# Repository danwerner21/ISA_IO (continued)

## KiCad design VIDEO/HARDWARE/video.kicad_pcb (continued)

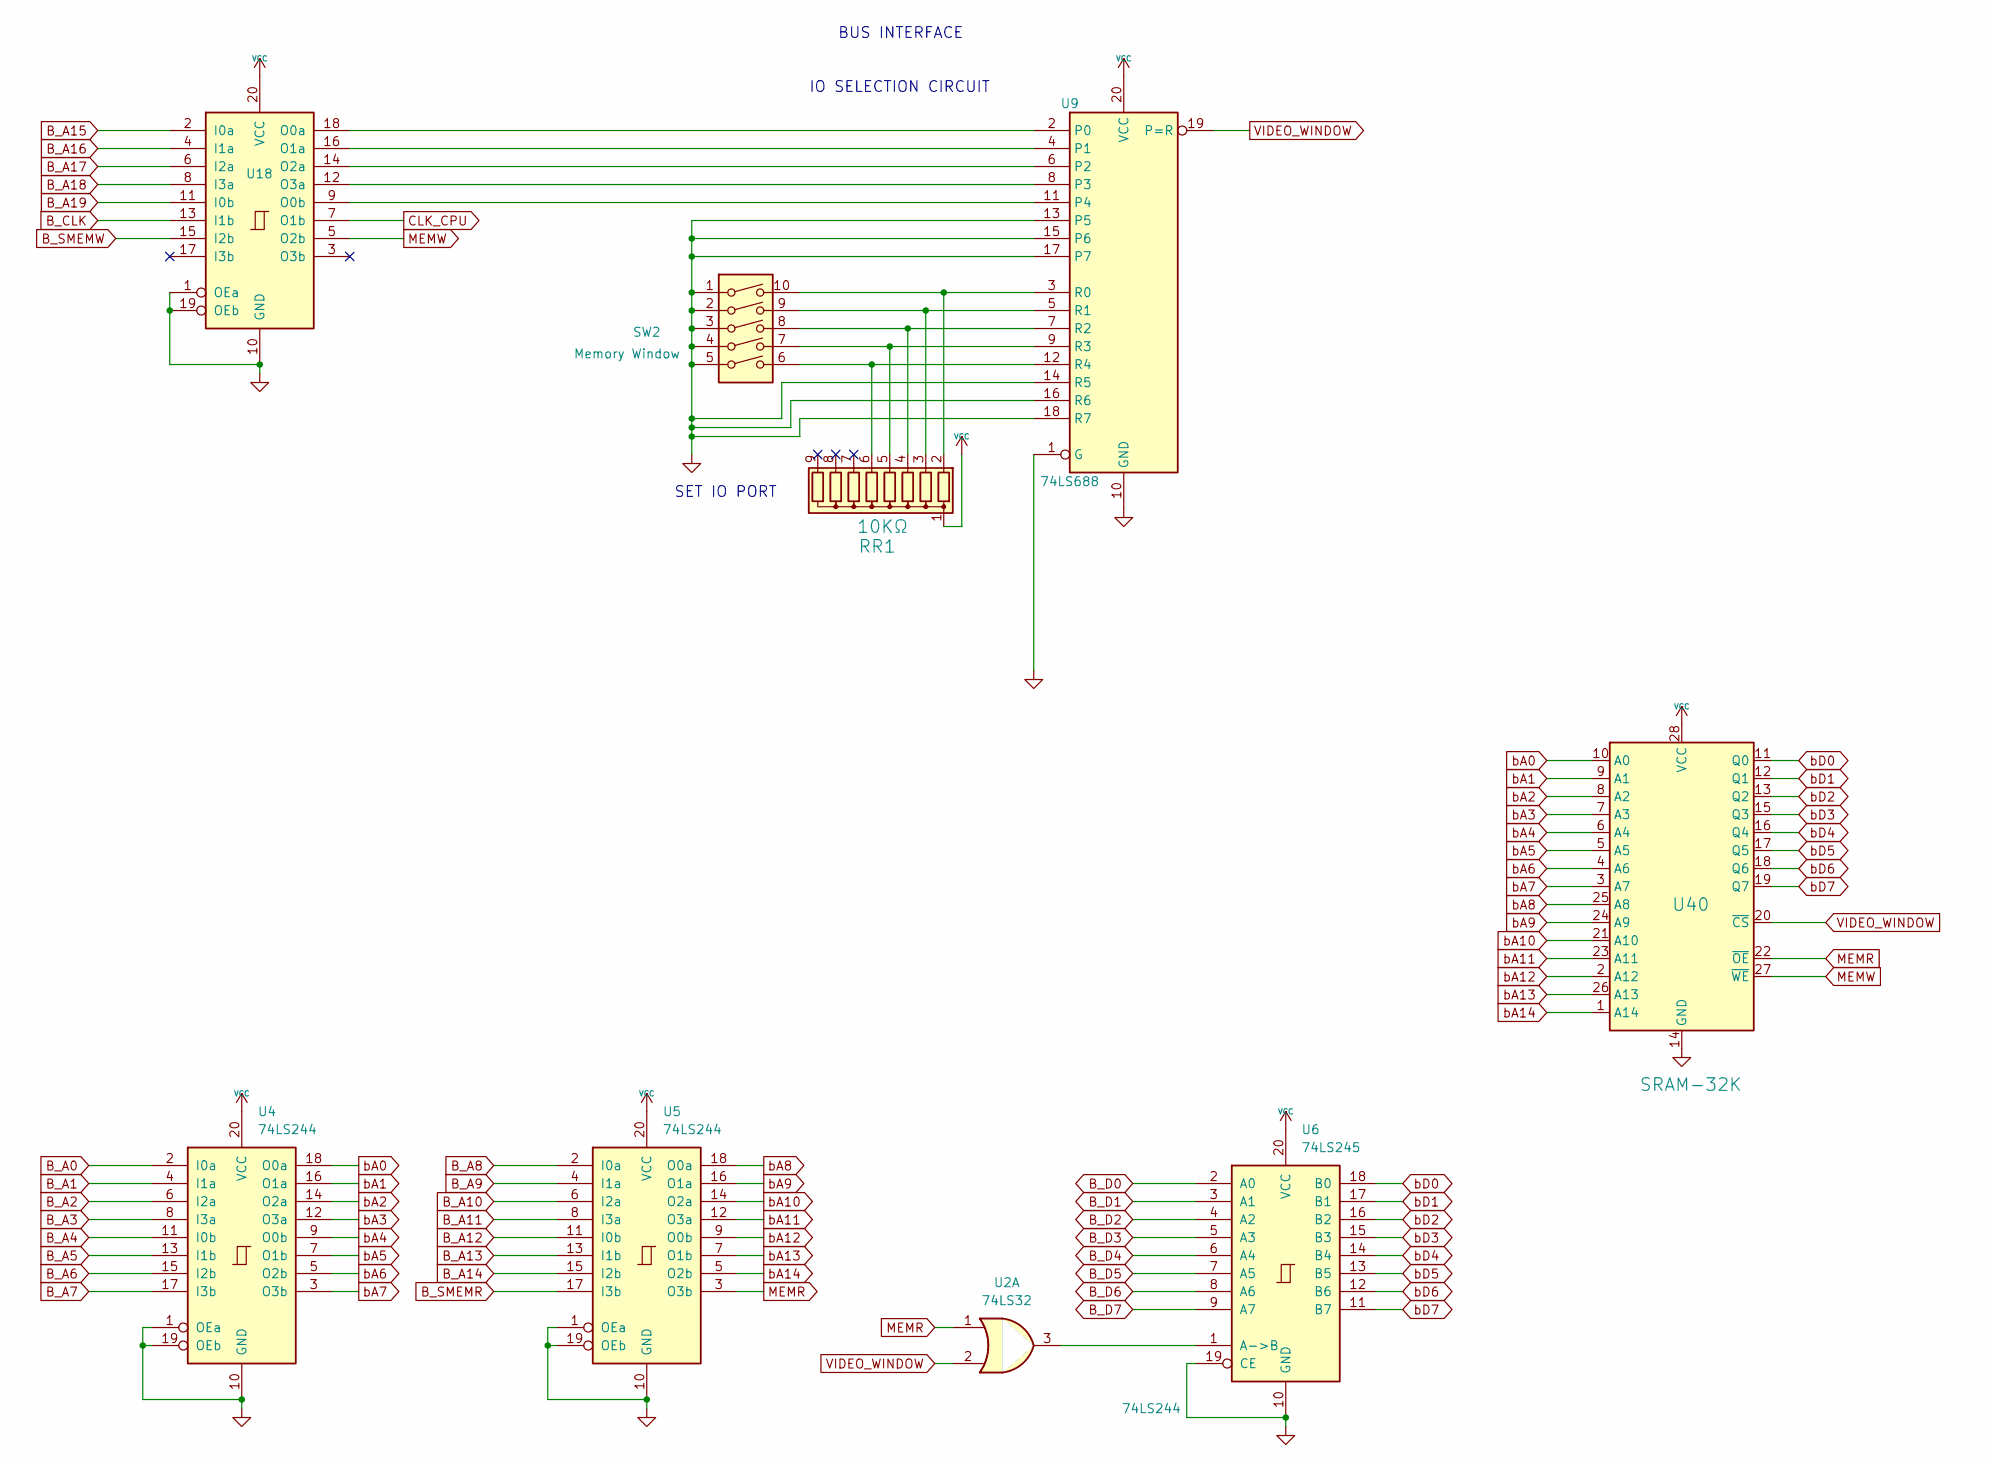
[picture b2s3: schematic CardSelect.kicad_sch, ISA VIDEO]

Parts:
RR1: 10KΩ; STD_DDW_SIP9
SW2: Memory Window; STD_DDW_DIP10
U2: 74LS32; STD_DDW_DIP14
U4, U5, U18: 74LS244; STD_DDW_DIP20
U6: 74LS245; STD_DDW_DIP20
U9: 74LS688; STD_DDW_DIP20
U40: SRAM-32K; STD_DDW_DIP28_SKINNY

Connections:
B_A0: U4.2 (I0a); also elsewhere on the board
B_A1: U4.4 (I1a); also elsewhere on the board
B_A2: U4.6 (I2a); also elsewhere on the board
B_A3: U4.8 (I3a); also elsewhere on the board
B_A4: U4.11 (I0b); also elsewhere on the board
B_A5: U4.13 (I1b); also elsewhere on the board
B_A6: U4.15 (I2b); also elsewhere on the board
B_A7: U4.17 (I3b); also elsewhere on the board
B_A8: U5.2 (I0a); also elsewhere on the board
B_A9: U5.4 (I1a); also elsewhere on the board
B_A10: U5.6 (I2a); also elsewhere on the board
B_A11: U5.8 (I3a); also elsewhere on the board
B_A12: U5.11 (I0b); also elsewhere on the board
B_A13: U5.13 (I1b); also elsewhere on the board
B_A14: U5.15 (I2b); also elsewhere on the board
B_A15: U18.2 (I0a); also elsewhere on the board
B_A16: U18.4 (I1a); also elsewhere on the board
B_A17: U18.6 (I2a); also elsewhere on the board
B_A18: U18.8 (I3a); also elsewhere on the board
B_A19: U18.11 (I0b); also elsewhere on the board
B_CLK: U18.13 (I1b); also elsewhere on the board
B_D0: U6.2 (A0); also elsewhere on the board
B_D1: U6.3 (A1); also elsewhere on the board
B_D2: U6.4 (A2); also elsewhere on the board
B_D3: U6.5 (A3); also elsewhere on the board
B_D4: U6.6 (A4); also elsewhere on the board
B_D5: U6.7 (A5); also elsewhere on the board
B_D6: U6.8 (A6); also elsewhere on the board
B_D7: U6.9 (A7); also elsewhere on the board
B_SMEMR: U5.17 (I3b); also elsewhere on the board
B_SMEMW: U18.15 (I2b); also elsewhere on the board
CLK_CPU: U18.7 (O1b); also elsewhere on the board
GND: SW2.1, SW2.2, SW2.3, SW2.4, SW2.5, U4.1 (OEa), U4.10 (GND), U4.19 (OEb), U5.1 (OEa), U5.10 (GND), U5.19 (OEb), U6.10 (GND), U6.19 (CE), U9.1 (G), U9.10 (GND), U9.13 (P5), U9.14 (R5), U9.15 (P6), U9.16 (R6), U9.17 (P7), U9.18 (R7), U18.1 (OEa), U18.10 (GND), U18.19 (OEb), U40.14 (GND); also elsewhere on the board
MEMR: U2.1, U5.3 (O3b), U40.22 (~OE)
MEMW: U18.5 (O2b), U40.27 (~WE); also elsewhere on the board
unnamed: RR1.2 (R1), SW2.10, U9.3 (R0)
unnamed: RR1.3 (R2), SW2.9, U9.5 (R1)
unnamed: RR1.4 (R3), SW2.8, U9.7 (R2)
unnamed: RR1.5 (R4), SW2.7, U9.9 (R3)
unnamed: RR1.6 (R5), SW2.6, U9.12 (R4)
unnamed: U2.3, U6.1 (A->B)
unnamed: U9.2 (P0), U18.18 (O0a)
unnamed: U9.11 (P4), U18.9 (O0b)
unnamed: U9.4 (P1), U18.16 (O1a)
unnamed: U9.6 (P2), U18.14 (O2a)
unnamed: U9.8 (P3), U18.12 (O3a)
VCC: RR1.1 (common), U4.20 (VCC), U5.20 (VCC), U6.20 (VCC), U9.20 (VCC), U18.20 (VCC), U40.28 (VCC); also elsewhere on the board
VIDEO_WINDOW: U2.2, U9.19 (P=R), U40.20 (~CS); also elsewhere on the board
bA0: U4.18 (O0a), U40.10 (A0)
bA1: U4.16 (O1a), U40.9 (A1)
bA2: U4.14 (O2a), U40.8 (A2)
bA3: U4.12 (O3a), U40.7 (A3)
bA4: U4.9 (O0b), U40.6 (A4)
bA5: U4.7 (O1b), U40.5 (A5)
bA6: U4.5 (O2b), U40.4 (A6)
bA7: U4.3 (O3b), U40.3 (A7)
bA8: U5.18 (O0a), U40.25 (A8)
bA9: U5.16 (O1a), U40.24 (A9)
bA10: U5.14 (O2a), U40.21 (A10)
bA11: U5.12 (O3a), U40.23 (A11)
bA12: U5.9 (O0b), U40.2 (A12)
bA13: U5.7 (O1b), U40.26 (A13)
bA14: U5.5 (O2b), U40.1 (A14)
bD0: U6.18 (B0), U40.11 (Q0); also elsewhere on the board
bD1: U6.17 (B1), U40.12 (Q1); also elsewhere on the board
bD2: U6.16 (B2), U40.13 (Q2); also elsewhere on the board
bD3: U6.15 (B3), U40.15 (Q3); also elsewhere on the board
bD4: U6.14 (B4), U40.16 (Q4); also elsewhere on the board
bD5: U6.13 (B5), U40.17 (Q5); also elsewhere on the board
bD6: U6.12 (B6), U40.18 (Q6); also elsewhere on the board
bD7: U6.11 (B7), U40.19 (Q7); also elsewhere on the board

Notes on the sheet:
SET IO PORT
IO SELECTION CIRCUIT
BUS INTERFACE

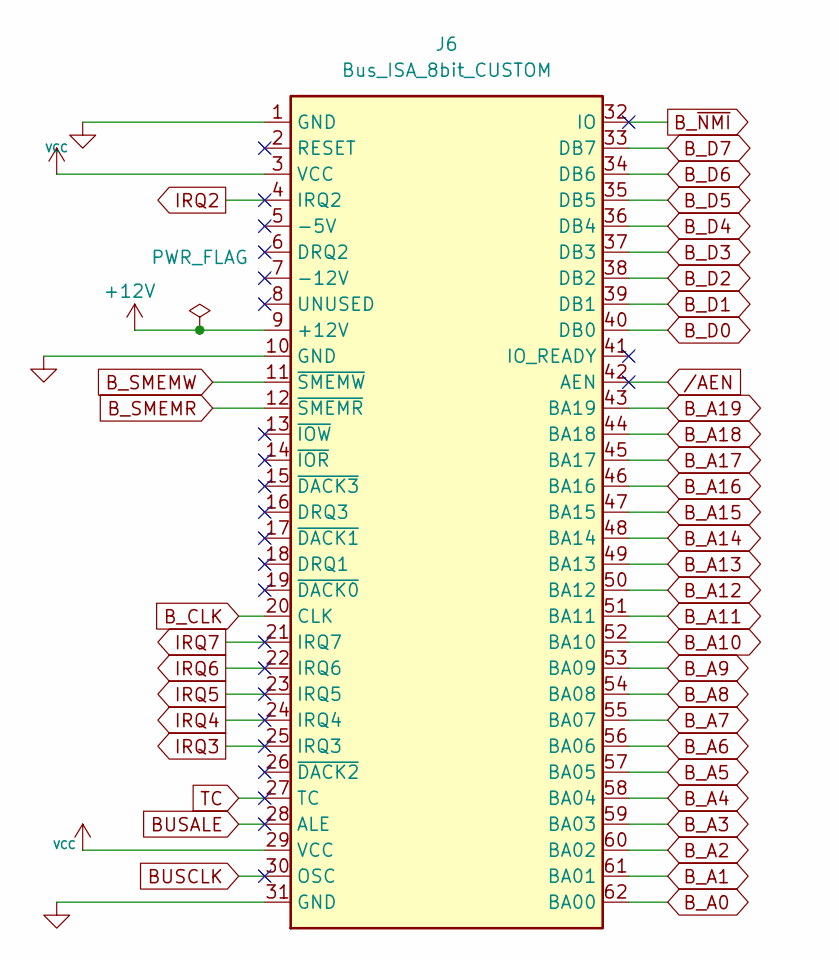
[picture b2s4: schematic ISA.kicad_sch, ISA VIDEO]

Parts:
J6: Bus_ISA_8bit_CUSTOM; BUSEDGE_XT

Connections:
+12V: J6.9 (+12V)
BUSALE: J6.28 (ALE)
BUSCLK: J6.30 (OSC)
B_A0: J6.62 (BA00); also elsewhere on the board
B_A1: J6.61 (BA01); also elsewhere on the board
B_A2: J6.60 (BA02); also elsewhere on the board
B_A3: J6.59 (BA03); also elsewhere on the board
B_A4: J6.58 (BA04); also elsewhere on the board
B_A5: J6.57 (BA05); also elsewhere on the board
B_A6: J6.56 (BA06); also elsewhere on the board
B_A7: J6.55 (BA07); also elsewhere on the board
B_A8: J6.54 (BA08); also elsewhere on the board
B_A9: J6.53 (BA09); also elsewhere on the board
B_A10: J6.52 (BA10); also elsewhere on the board
B_A11: J6.51 (BA11); also elsewhere on the board
B_A12: J6.50 (BA12); also elsewhere on the board
B_A13: J6.49 (BA13); also elsewhere on the board
B_A14: J6.48 (BA14); also elsewhere on the board
B_A15: J6.47 (BA15); also elsewhere on the board
B_A16: J6.46 (BA16); also elsewhere on the board
B_A17: J6.45 (BA17); also elsewhere on the board
B_A18: J6.44 (BA18); also elsewhere on the board
B_A19: J6.43 (BA19); also elsewhere on the board
B_CLK: J6.20 (CLK); also elsewhere on the board
B_D0: J6.40 (DB0); also elsewhere on the board
B_D1: J6.39 (DB1); also elsewhere on the board
B_D2: J6.38 (DB2); also elsewhere on the board
B_D3: J6.37 (DB3); also elsewhere on the board
B_D4: J6.36 (DB4); also elsewhere on the board
B_D5: J6.35 (DB5); also elsewhere on the board
B_D6: J6.34 (DB6); also elsewhere on the board
B_D7: J6.33 (DB7); also elsewhere on the board
B_SMEMR: J6.12 (~SMEMR); also elsewhere on the board
B_SMEMW: J6.11 (~SMEMW); also elsewhere on the board
B_~NMI: J6.32 (IO)
GND: J6.1 (GND), J6.10 (GND), J6.31 (GND); also elsewhere on the board
IRQ2: J6.4 (IRQ2)
IRQ3: J6.25 (IRQ3)
IRQ4: J6.24 (IRQ4)
IRQ5: J6.23 (IRQ5)
IRQ6: J6.22 (IRQ6)
IRQ7: J6.21 (IRQ7)
TC: J6.27 (TC)
VCC: J6.3 (VCC), J6.29 (VCC); also elsewhere on the board
/AEN: J6.42 (AEN)

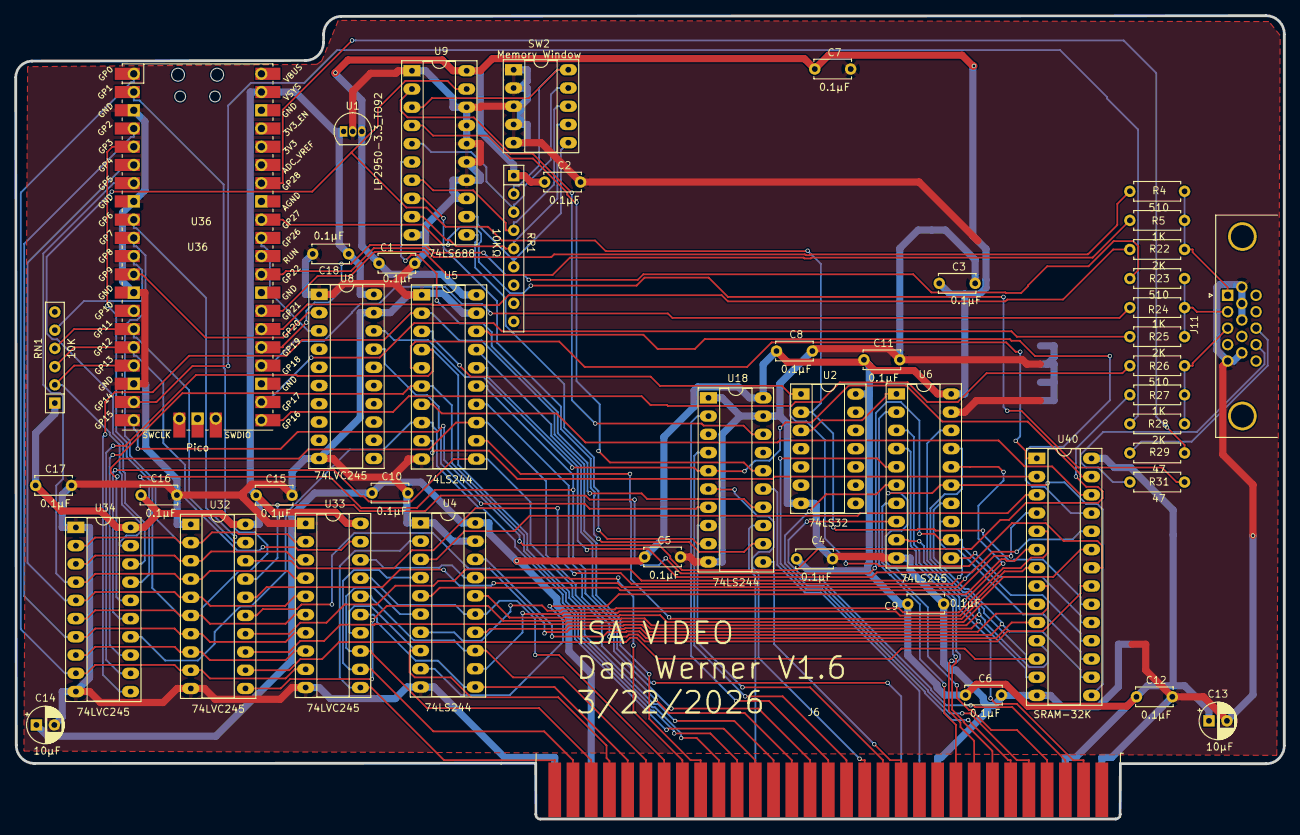
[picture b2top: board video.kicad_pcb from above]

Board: 2 copper layers, 176.7 x 111.9 mm, 47 parts (0 on the bottom side), 102 nets.

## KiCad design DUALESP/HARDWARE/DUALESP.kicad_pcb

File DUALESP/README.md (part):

# ESP32 Multi IO
The Nhyodyne ESP32 board provides the following functions for your Nhyodyne computer
* ANSI Console
* Graphics
* Sprites
* Sound
* Dual USB Serial Support
* WiFi
* Keyboard
* Mouse

This board relies heavily on the FabGL library from Fabrizio Di Vittorio.   More information can be found [HERE](http://www.fabglib.org/)

# BUGS

Version 1.0 is unusable

Version 1.1 is missing some data line connections
* Connect U11 Pin 11 to U13 Pin 15
* Connect U11 Pin 12 to U13 Pin 1
* Connect U11 Pin 13 to U13 Pin 2
* Connect U11 Pin 14 to U13 Pin 3
* Connect U11 Pin 3 to U13 Pin 4
* Connect U11 Pin 4 to U13 Pin 5
* Connect U11 Pin 5 to U13 Pin 6
* Connect U11 Pin 6 to U13 Pin 7

Version 1.2 has not been verified, but should be correct

# ESP32 BOM
Qty|Reference(s)|Value|Notes
---|------------|-----|-----
12|C1, C2, C3, C4, C5, C6, C7, C8, C9, C10, C13, C14|0.1uF
3|C11, C12, C16|10uF
1|C15|100nf
1|D2|LED
2|D3, D6|1N4001
1|J3|Pin Header, right angle 1x2
1|J4|Pin Header, right angle 1x3
1|J5|Pin Header, right angle 1x3
1|J6|DB15 Female High Density PCB VGA Connector
1|J7|Pin Header, right angle 2x5
1|P2|Pin Header Right Angle 2x25
4|R1, R3, R14, R15|120ohm
1|R2|470ohm
2|R4, R6|2Kohm
2|R5, R13|1Kohm
3|R7, R9, R11|400ohm
3|R8, R10, R12|800ohm
1|R16|270ohm
1|R17|150ohm
1|RR1|10Kohm, networked, 9 pin, 8 resistor
1|RR2|1Kohm, networked, 9 pin, 8 resistor
1|SW1|8 position DIP switch
1|U1|74LS04
2|U2, U4|74LS244
1|U3|74LS245
3|U5, U6, U14|74LS32
2|U7, U9|74HC595
2|U8, U11|74HC165
1|U10|74LS688
2|U12, U13|ESP-WROOM-32 Dev Module|Such As: https://www.amazon.com/ESP-WROOM-32-Development-Microcontroller-Integrated-Compatible/dp/B08D5ZD528
1|U15|74LS244
1|U16|74LS07

# ESP32 Firmware Installation
The firmware for this board requires that platformio be installed on your system.

To install platformio core for your operating system see the directions [HERE](https://platformio.org/install/cli).  
Make sure you follow the additional directions to install the shell commands.

On linux systems it may be necessary to update permissions for the device that is autocreated for the ESP32. [More details](https://docs.platformio.org/en/latest/core/installation/udev-rules.html)  
Once platformio is properly setup on your system, you should be able to build and deploy the firmware to the ESP32.  

## To build and install the ESP firmware:
Take the ESP32 device you have designated as ESP0 and with it NOT INSTALLED in the nhyodyne card, plug it into your computer via USB.
change directory to the ESP0Firmware folder on your PC and from the operating system prompt type
```
pio run -t upload
```

Over the next couple of minutes you should see the build and upload process
something like this:

```
dwerner@lserver02:/lserver03/fileserv/Development/Vintage/Projects/nhyodyne/Z80ESP/ESP0Firmware$ pio run -t upload
Processing esp32dev (platform: espressif32; board: esp32dev; framework: arduino)
-----------------------------------------------------------------------------------------------------------------------
Verbose mode can be enabled via `-v, --verbose` option
CONFIGURATION: https://docs.platformio.org/page/boards/espressif32/esp32dev.html
PLATFORM: Espressif 32 (6.3.2) > Espressif ESP32 Dev Module
HARDWARE: ESP32 240MHz, 320KB RAM, 4MB Flash
DEBUG: Current (cmsis-dap) External (cmsis-dap, esp-bridge, esp-prog, iot-bus-jtag, jlink, minimodule, olimex-arm-usb-ocd, olimex-arm-usb-ocd-h, olimex-arm-usb-tiny-h, olimex-jtag-tiny, tumpa)
PACKAGES:
 - framework-arduinoespressif32 @ 3.20009.0 (2.0.9)
 - tool-esptoolpy @ 1.40501.0 (4.5.1)
 - tool-mkfatfs @ 2.0.1
 - tool-mklittlefs @ 1.203.210628 (2.3)
 - tool-mkspiffs @ 2.230.0 (2.30)
 - toolchain-xtensa-esp32 @ 8.4.0+2021r2-patch5
LDF: Library Dependency Finder -> https://bit.ly/configure-pio-ldf
LDF Modes: Finder ~ deep+, Compatibility ~ soft
Found 34 compatible libraries
Scanning dependencies...
Dependency Graph
|-- FabGL @ 1.0.9
|-- SPI @ 2.0.0
|-- Preferences @ 2.0.0
Building in release mode
Retrieving maximum program size .pio/build/esp32dev/firmware.elf
Checking size .pio/build/esp32dev/firmware.elf
Advanced Memory Usage is available via "PlatformIO Home > Project Inspect"
RAM:   [=         ]   9.3% (used 30632 bytes from 327680 bytes)
Flash: [=====     ]  46.4% (used 608561 bytes from 1310720 bytes)
Configuring upload protocol...
AVAILABLE: cmsis-dap, esp-bridge, esp-prog, espota, esptool, iot-bus-jtag, jlink, minimodule, olimex-arm-usb-ocd, olimex-arm-usb-ocd-h, olimex-arm-usb-tiny-h, olimex-jtag-tiny, tumpa
CURRENT: upload_protocol = esptool
Looking for upload port...
Auto-detected: /dev/ttyUSB0
Uploading .pio/build/esp32dev/firmware.bin
esptool.py v4.5.1
Serial port /dev/ttyUSB0
Connecting.....
Chip is ESP32-D0WD-V3 (revision v3.0)
Features: WiFi, BT, Dual Core, 240MHz, VRef calibration in efuse, Coding Scheme None
Crystal is 40MHz
MAC: 08:b6:1f:33:39:fc
Uploading stub...
Running stub...
Stub running...
Changing baud rate to 460800
Changed.
Configuring flash size...
Flash will be erased from 0x00001000 to 0x00005fff...
Flash will be erased from 0x00008000 to 0x00008fff...
Flash will be erased from 0x0000e000 to 0x0000ffff...
Flash will be erased from 0x00010000 to 0x000a4fff...
Compressed 17488 bytes to 12168...
Writing at 0x00001000... (100 %)
Wrote 17488 bytes (12168 compressed) at 0x00001000 in 0.5 seconds (effective 287.3 kbit/s)...
Hash of data verified.
Compressed 3072 bytes to 146...
Writing at 0x00008000... (100 %)
Wrote 3072 bytes (146 compressed) at 0x00008000 in 0.0 seconds (effective 571.2 kbit/s)...
Hash of data verified.
Compressed 8192 bytes to 47...
Writing at 0x0000e000... (100 %)
Wrote 8192 bytes (47 compressed) at 0x0000e000 in 0.1 seconds (effective 829.3 kbit/s)...
Hash of data verified.
Compressed 608928 bytes to 309667...
Writing at 0x00010000... (5 %)
Writing at 0x00020854... (10 %)
Writing at 0x0002f631... (15 %)
Writing at 0x0003b66a... (21 %)
Writing at 0x0004b725... (26 %)
Writing at 0x00050794... (31 %)
Writing at 0x00056585... (36 %)
Writing at 0x0005c2fd... (42 %)
Writing at 0x0006271e... (47 %)
Writing at 0x000684b2... (52 %)
Writing at 0x0006dceb... (57 %)
Writing at 0x00073098... (63 %)
Writing at 0x0007864e... (68 %)
Writing at 0x0007de33... (73 %)
Writing at 0x0008412b... (78 %)
Writing at 0x0008c053... (84 %)
Writing at 0x00094cba... (89 %)
Writing at 0x0009a559... (94 %)
Writing at 0x0009f9b7... (100 %)
Wrote 608928 bytes (309667 compressed) at 0x00010000 in 8.0 seconds (effective 606.6 kbit/s)...
Hash of data verified.

Leaving...
Hard resetting via RTS pin...
============================================ [SUCCESS] Took 22.49 seconds ============================================
```

Once this is done you can install ESP0 into U12 on your nhyodyne board.  Then repeat the process for the ESP1 and install into U13.

# ESP32 Communication Protocol

The ESP32 board communicates with your system via 3 ports, two IO ports and one status port.

The default configuration sets the base IO to $9C.  IO Communication with ESP0 is at base port, ESP1 is at base port +1 and the status register is at base port +2.

```
ESPBASE         EQU $9C         ; Base Port
ESP0:           EQU ESPBASE     ; ESP0 IO PORT

ESP1:           EQU ESPBASE+1   ; ESP1 IO PORT

ESP_STATUS:     EQU ESPBASE+2   ; ESP  STATUS PORT
                                ; MSB XX XX S S S S S
                                ;           | | | | |- ESP0 READY_OUTPUT
                                ;           | | | |--- ESP0 BUSY
                                ;           | | |----- ESP0 SPARE (unused)
                                ;           | |------- ESP1 READY_OUTPUT
                                ;           |--------- ESP1 BUSY
```

The communication process is fairly straight forward.  Upon reset, the ESP will initialize, set BUSY and READY_OUTPUT to low and wait for an opcode.

To send an opcode or data to the ESP:

* wait for ESPx BUSY bit to go low (a timeout is suggested)
* write the opcode or data to the ESPx IO port
* it is a best practice to wait for ESPx BUSY bit to go high then low (a timeout is suggested) before sending the next byte

If an "out of sync" occurrs, where the ESP is waiting for data rather than an opcode and the host driver is unsure of the state of the ESP, it is possible to resync the ESP back to the "waiting for opcode" state by sending a stream of NULL bytes to the IO port. A stream of more than 25 NULLS should always safely return the ESP back to the "waiting for opcode" state.

Some Opcodes will return one or more bytes to the host system.   For those opcodes

* wait for ESPx BUSY bit to go low (a timeout is suggested)
* wait for ESPx READY_OUTPUT bit to go high (a timeout is suggested)
* Read the ESPx IO port
* it is a best practice to wait for ESPx BUSY bit to go high then low (a timeout is suggested) before sending the next byte

Note that the BUSY bit transitions after a command is written or data is read can happen very fast.   On slower systems a timeout is required as it is possible for the host system to miss this transition if it is not polling fast enough.

It is also a best practice to empty the ESP send buffer before sending an opcode that returns data.

For example code, see the ESPTEST.ASM program in this repo.

# ESP32 ESP0 Opcode Reference

## ESP32 Misc Opcodes

OP CODE|Description|Values
-------|-----------|------
00|NO OPERATION|NONE

The NO OPERATION opcode is used to sync the ESP32 communications stream to a known state, "Waiting for opcode".

Input Parameters: None  
Returns: None  

OP CODE|Description|Values
-------|-----------|------
255|DISCOVER|"E" "S" "P" "3" "2" "V" "1"

The DISCOVER opcode is used by host systems to verify the presence and version of the ESP hardware and firmware.

Input Parameters: None  
Returns: 7 bytes - "E" "S" "P" "3" "2" "V" "1"  

## ESP32 Terminal Opcodes
	
OP CODE|Description|Values
-------|-----------|------
1 |VGA ANSI TERM OUT SINGLE CHAR| OUT-BYTE

The VGA ANSI TERM OUT SINGLE CHAR opcode sends a single byte to the ANSI terminal subsystem of the ESP32.  Using the ANSI escape sequence set, this byte is rendered to the VGA terminal console.

Input Parameters: 1 byte - "OUT CHAR"  
Returns: None  

OP CODE|Description|Values
-------|-----------|------
2 |VGA ANSI TERM OUT NULL TERMINATED STRING| OUT-BYTE	OUT-BYTE	OUT-BYTE	OUT-BYTE	OUT-BYTE	OUT-BYTE	…	…	…	…	NULL

The VGA ANSI TERM OUT NULL TERMINATED STRING opcode sends a null terminated string to the ANSI terminal subsystem of the ESP32.  Using the ANSI escape sequence set, this string is rendered to the VGA terminal console.

Input Parameters: X bytes - string terminated by a null  
Returns: None  

OP CODE|Description|Values
-------|-----------|------
3 |VGA ANSI TERM KEYBOARD IN| IN-BYTE	

The VGA ANSI TERM KEYBOARD IN opcode returns a byte from the terminal keyboard buffer.   If there is no keystrokes in the buffer, the opcode will return a null.

Input Parameters: None  
Returns: 1 byte - input keystroke or null  

OP CODE|Description|Values
-------|-----------|------
4 |VGA ANSI TERM KEYBOARD BUFFER LENGTH| IN-BYTE

The VGA ANSI TERM KEYBOARD BUFFER LENGTH opcode returns the numbser of keystrokes in the ANSI terminal keyboard buffer.

Input Parameters: None  
Returns: 1 byte - keystroke buffer length  

OP CODE|Description|Values
-------|-----------|------
5 |VGA ANSI TERM SET CURSOR| OUT-BYTE

The VGA ANSI TERM SET CURSOR opcode sets the visibility of the terminal cursor.
* 0 = cursor off
* 1 = cursor on

Input Parameters: 1 byte - Cursor status  
Returns: None  

## ESP32 Serial Opcodes

OP CODE|Description|Values
-------|-----------|------
6 |Set Baud Rate| OUT-BYTE  OUT-BYTE  OUT-BYTE  OUT-BYTE

The Set Baud Rate opcode sets the baud rate for the ESP async serial port.  This port is exposed through the header on the top of the card and through the USB port on the ESP32 module.   Byte order is least signifigant byte to most significant byte.

Input Parameters: 4 bytes - Baud Rate
Returns: None  

OP CODE|Description|Values
-------|-----------|------
7 |Set Serial Mode| OUT-BYTE

The Set Serial Mode opcode sets the serial communication parameters for the ESP async serial port.  This port is exposed through the header on the top of the card and through the USB port on the ESP32 module.
Parameters are set as follows:
* 0 = 8 data bits, no parity, 1 stop bits
* 1 = 8 data bits, even parity, 1 stop bits
* 2 = 8 data bits, odd parity, 1 stop bits
* 3 = 7 data bits, no parity, 1 stop bits
* 4 = 7 data bits, even parity, 1 stop bits
* 5 = 7 data bits, odd parity, 1 stop bits

Input Parameters: 1 byte - Serial Mode  
Returns: None  

OP CODE|Description|Values
-------|-----------|------
8 |Serial TX Single char| OUT-BYTE

The Serial TX Single char opcode transmits a single byte through the serial communication port.  This port is exposed through the header on the top of the card and through the USB port on the ESP32 module.

Input Parameters: 1 byte - char  
Returns: None  

OP CODE|Description|Values
-------|-----------|------
9 |Serial TX Null Terminated String| OUT-BYTE  OUT-BYTE  OUT-BYTE  OUT-BYTE  OUT-BYTE  OUT-BYTE	…	…	…	…	NULL

The Serial TX Null Terminated String opcode transmits a null terminated string through the serial communication port.  This port is exposed through the header on the top of the card and through the USB port on the ESP32 module.

Input Parameters: X bytes - string terminated by a null  
Returns: None  

OP CODE|Description|Values
-------|-----------|------
10 |Serial RX| IN-BYTE

The Serial RX opcode returns a byte from the serial communication port buffer.  If there are no values in the buffer, the opcode will return a null.  This port is exposed through the header on the top of the card and through the USB port on the ESP32 module.   

Input Parameters: None  
Returns: 1 byte - input value or null    

OP CODE|Description|Values
-------|-----------|------
11 |Chars in Serial Buffer| IN-BYTE

The Chars in Serial Buffer opcode returns the numbser of keystrokes in the serial communication port buffer.  This port is exposed through the header on the top of the card and through the USB port on the ESP32 module.   

Input Parameters: None  
Returns: 1 byte - serial buffer length  

## ESP32 Audio Opcodes

OP CODE|Description|Values
-------|-----------|------
12 |Play Null Terminated String| OUT-BYTE  OUT-BYTE  OUT-BYTE  OUT-BYTE  OUT-BYTE  OUT-BYTE	…	…	…	…	NULL

The Play Null Terminated String opcode intreprets a string as musical notes and plays them with a square wave tone generator through the audio port on the top of the ESP32 card.  The audio port is at line level and requires amplification. 

Example string: "A4 4 2 A4 4 2 A#4 4 2 C5 4 2 C5 4 2 A#4 4 2 A4 4 2 G4 4 2 F4 4 2 F4 4 2 G4 4 2 A4 4 2 A4 2 2 G4 16 2 G4 2 2 P 8 2 "

The string is in the format:  [note (C,D,E,F,G,A,B) + [#,b] + octave (2..7) + space + tempo (99..1)] + [pause (P) + space + tempo (99.1)]
```
    "A4 4 2" 
     |  | |----- Tempo
     |  |------- Octave (2..7)
     |---------- note to play (or P for pause)
```     

Input Parameters: 1 byte - Cursor status  
Returns: None  

OP CODE|Description|Values
-------|-----------|------
13 |Play Sound	| OUT-BYTE  OUT-BYTE  OUT-BYTE  OUT-BYTE  OUT-BYTE  OUT-BYTE  OUT-BYTE  OUT-BYTE  OUT-BYTE  OUT-BYTE  OUT-BYTE  OUT-BYTE  OUT-BYTE  OUT-BYTE  OUT-BYTE  OUT-BYTE  OUT-BYTE  OUT-BYTE  OUT-BYTE  OUT-BYTE  OUT-BYTE  OUT-BYTE  OUT-BYTE  OUT-BYTE  

The Play Sound opcode plays a sound with the specified parameters through the audio port on the top of the ESP32 card.  The audio port is at line level and requires amplification. 

The following parameters need to be specified in the following order:
* Attack, 4 bytes, Byte order is least signifigant byte to most significant byte.
* Decay, 4 bytes, Byte order is least signifigant byte to most significant byte.
* Sustain, 2 bytes, Byte order is least signifigant byte to most significant byte.
* Release, 4 bytes, Byte order is least signifigant byte to most significant byte.
* WaveType, 1 byte,   0=WAVE_SQUARE,1=WAVE_SINE,2=WAVE_TRIANGLE,3=WAVE_SAW,4=WAVE_NOISE
* Volume, 2 bytes,  Byte order is least signifigant byte to most significant byte.  Even though volume is specified as two bytes, only LSB is used.
* Duration, 2 bytes, Byte order is least signifigant byte to most significant byte.  Duration is in MS.
* FreqStart, 2 bytes, Byte order is least signifigant byte to most significant byte.
* FreqEnd, 2 bytes, Byte order is least signifigant byte to most significant byte.
* ModFreqMode, 1 byte,  0=MODFREQ_NONE,1=MODFREQ_TO_END,2=MODFREQ_TO_RELEASE,3=MODFREQ_TO_SUSTAIN

More detailed information about programming the sound generator can be found [HERE](http://www.fabglib.org/classfabgl_1_1_sound_generator.html)

Input Parameters: 24 bytes
Returns: None  

OP CODE|Description|Values
-------|-----------|------
14 |Set Volume| OUT-BYTE

The Set Volume opcode sets the overall volume of the sound generated by the audio port on the top of the ESP32 card.  The audio port is at line level and requires amplification.

Input Parameters: 1 byte - Volume
Returns: None  

## ESP32 Graphics Opcodes
OP CODE|Description|Values
-------|-----------|------
15 |Set Display Resolution| OUT-BYTE

The Set Display Resolution opcode sets the display resolution of the VGA output of the ESP32. The specified display resolution is stored in flash memory and will survive a power cycle.  Note that this opcode can take a SECOND OR MORE to process as it requires the ESP to reboot, so leave plenty of time after issuing this command. ALWAYS issue a Clear Display(17) command after changing video mode. 

The proper sequence is as follows:
* issue Set Display Resolution opcode
* send one byte for new video mode
* wait at least 3 seconds
* issue clear display command

ID|Mode Name|Description|Color Depth
--|---------|-----------|-----------
00|VGA_320x200_70Hz|320x200@70Hz resolution - the same of VGA_640x200_70Hz with horizontal halved|64
01|VGA_320x200_75Hz|320x200@75Hz resolution|64
02|VGA_320x200_75HzRetro|320x200@75Hz retro resolution|64
03|QVGA_320x240_60Hz|320x240@60Hz resolution|64
04|VGA_400x300_60Hz|400x300@60Hz resolution|64
05|VGA_480x300_75Hz|480x300@75Hz resolution|64
06|VGA_512x192_60Hz|512x192@60Hz resolution|16
07|VGA_512x384_60Hz	|512x384@60Hz resolution|16
08|VGA_512x448_60Hz|512x448@60Hz resolution|16
09|VGA_512x512_58Hz|512x512@58Hz resolution|16
10|VGA_640x200_60HzD|640x200@60Hz doublescan resolution|16
11|VGA_640x200_70Hz|640x200@70Hz resolution - the same of VGA_640x400_70Hz with vertical halved|16
12|VGA_640x200_70HzRetro|640x200@70Hz retro resolution|16
13|VGA_640x240_60Hz|640x240@60Hz (DoubleScan) resolution|16
14|VGA_640x350_70Hz|640x350@70Hz resolution|16
15|VGA_640x350_70HzAlt1|640x350@70HzAlt1 resolution|16
16|VESA_640x350_85Hz|640x350@85Hz resolution|16
17|VGA_640x382_60Hz|640x382@60Hz resolution|16
18|VGA_640x384_60Hz|640x384@60Hz resolution|16
19|VGA_640x400_70Hz|640x400@70Hz resolution|16
20|VGA_640x400_60Hz|640x400@60Hz (actually 640x480 but with less lines)|16
21|VGA_640x480_60Hz|640x480@60Hz resolution|16
22|VGA_640x480_60HzAlt1|640x480@60HzAlt1 resolution|16
23|VGA_640x480_60HzD|640x480@60Hz doublescan resolution|16
24|VGA_640x480_73Hz|640x480@73Hz resolution|16
25|VESA_640x480_75Hz|640x480@75Hz resolution|16
26|VGA_720x348_50HzD|720x348@50Hz doublescan resolution|16
27|VGA_720x348_59HzD|720x348@59Hz doublescan resolution|16
28|VGA_720x348_73Hz|720x348@73Hz resolution|16
29|VGA_720x350_70Hz|720x350@70Hz resolution|16
30|VGA_720x400_70Hz|720x400@70Hz resolution|16
31|VESA_720x400_85Hz|720x400@85Hz resolution|16
32|PAL_720x576_50Hz|720x576@50Hz resolution|8
33|VESA_768x576_60Hz|768x576@60Hz resolution|8
34|SVGA_800x300_60Hz|800x300@60Hz resolution|8
35|SVGA_800x600_56Hz|800x600@56Hz resolution|4
36|SVGA_800x600_60Hz|800x600@60Hz resolution|4
37|SVGA_960x540_60Hz|960x540@60Hz resolution|4
38|SVGA_1024x768_60Hz|1024x768@60Hz resolution|2
39|SVGA_1024x768_70Hz|1024x768@70Hz resolution|2
40|SVGA_1024x768_75Hz|1024x768@75Hz resolution|2
41|SVGA_1280x600_60Hz|1280x600@60Hz resolution|2
42|SVGA_1280x720_60Hz|1280x720@60Hz resolution|2
43|SVGA_1280x720_60HzAlt1|1280x720@60Hz resolution|2
44|SVGA_1280x768_50Hz|1280x768@50Hz resolution|2

Input Parameters: 1 byte - Video Mode
Returns: None  

OP CODE|Description|Values
-------|-----------|------
16 |Load Font| OUT-BYTE

The Load Font opcode sets the display font for the VGA ANSI Terminal.

ID|Font Name	
--|---------
00|FONT_4X6
01|FONT_5X7
02|FONT_5X8
03|FONT_6X8
04|FONT_6X9
05|FONT_6X10
06|FONT_6X12
07|FONT_6X13
08|FONT_7X13
09|FONT_7X14
10|FONT_8X8
11|FONT_8X9
12|FONT_8X13
13|FONT_8X14
14|FONT_8X16
15|FONT_8X19
16|FONT_9X15
17|FONT_9X18
18|FONT_10X20
19|FONT_BIGSERIF_8X14
20|FONT_BIGSERIF_8X16
21|FONT_BLOCK_8X14
22|FONT_BROADWAY_8X14
23|FONT_COMPUTER_8X14
24|FONT_COURIER_8X14
25|FONT_LCD_8X14
26|FONT_OLDENGL_8X16
27|FONT_SANSERIF_8X14
28|FONT_SANSERIF_8X16
29|FONT_SLANT_8X14
30|FONT_WIGGLY_8X16

Input Parameters: 1 byte - Font
Returns: None  

OP CODE|Description|Values
-------|-----------|------
17|Clear Display| NONE

The Clear Display opcode clears the VGA.

Input Parameters: None
Returns: None  

OP CODE|Description|Values
-------|-----------|------
18 |Copy Rectangle| OUT-BYTE OUT-BYTE OUT-BYTE OUT-BYTE OUT-BYTE OUT-BYTE OUT-BYTE OUT-BYTE OUT-BYTE OUT-BYTE OUT-BYTE OUT-BYTE

The Copy Rectangle opcode copyies a rectangle shaped area from one part of the bitmapped display to another.

The following parameters need to be specified in the following order:
* Source X coordinate, 2 bytes, Byte order is least signifigant byte to most significant byte.
* Source Y coordinate, 2 bytes, Byte order is least signifigant byte to most significant byte.
* Destination X coordinate, 2 bytes, Byte order is least signifigant byte to most significant byte.
* Destination Y coordinate, 2 bytes, Byte order is least signifigant byte to most significant byte.
* Area Width, 2 bytes, Byte order is least signifigant byte to most significant byte.
* Area Hight, 2 bytes, Byte order is least signifigant byte to most significant byte.

All Parameters above are in display pixels with 0,0 being the upper left of the VGA screen.

Input Parameters: 12 bytes
Returns: None  

OP CODE|Description|Values
-------|-----------|------
19 |Draw Bitmap| OUT-BYTE(s)

The Draw Bitmap opcode draws a specified bitmap on the VGA display.

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
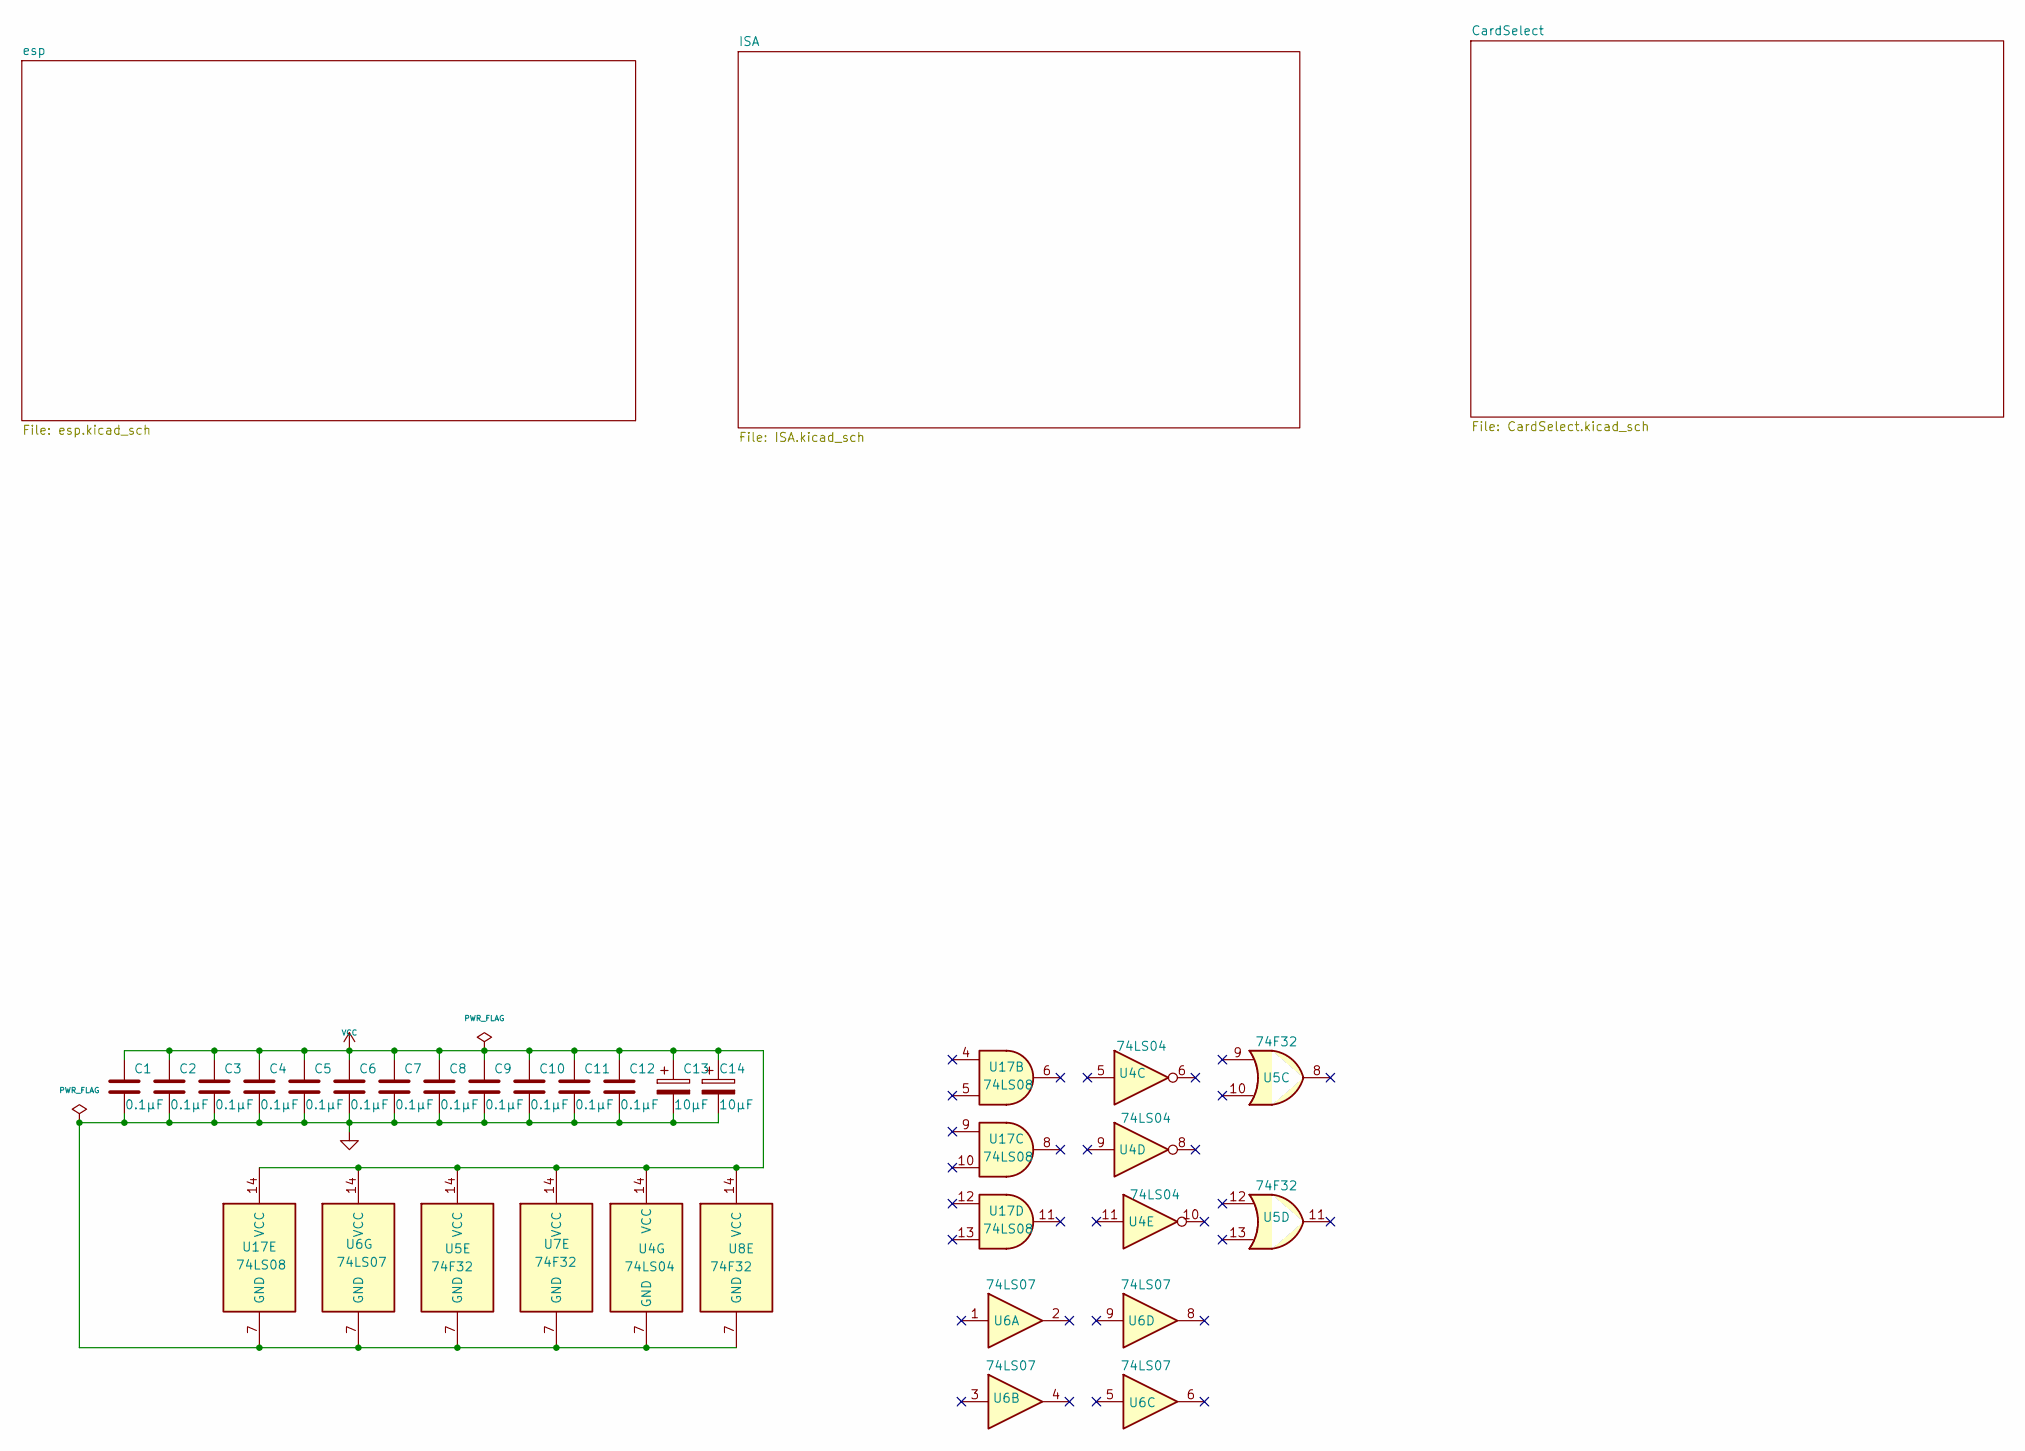
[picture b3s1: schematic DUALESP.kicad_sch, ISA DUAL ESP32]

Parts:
C1, C2, C3, C4, C5, C6, C7, C8, C9, C10, C11, C12: 0.1µF; STD_DDW_CAP
C13, C14: 10µF; STD_DDW_PCAP
U4: 74LS04; STD_DDW_DIP14
U5, U7, U8: 74F32; STD_DDW_DIP14
U6: 74LS07; STD_DDW_DIP14
U17: 74LS08; STD_DDW_DIP14

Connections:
GND: C1.2, C2.2, C3.2, C4.2, C5.2, C6.2, C7.2, C8.2, C9.2, C10.2, C11.2, C12.2, C13.2, C14.2, U4.7 (GND), U5.7 (GND), U6.7 (GND), U7.7 (GND), U8.7 (GND), U17.7 (GND); also elsewhere on the board
VCC: C1.1, C2.1, C3.1, C4.1, C5.1, C6.1, C7.1, C8.1, C9.1, C10.1, C11.1, C12.1, C13.1, C14.1, U4.14 (VCC), U5.14 (VCC), U6.14 (VCC), U7.14 (VCC), U8.14 (VCC), U17.14 (VCC); also elsewhere on the board

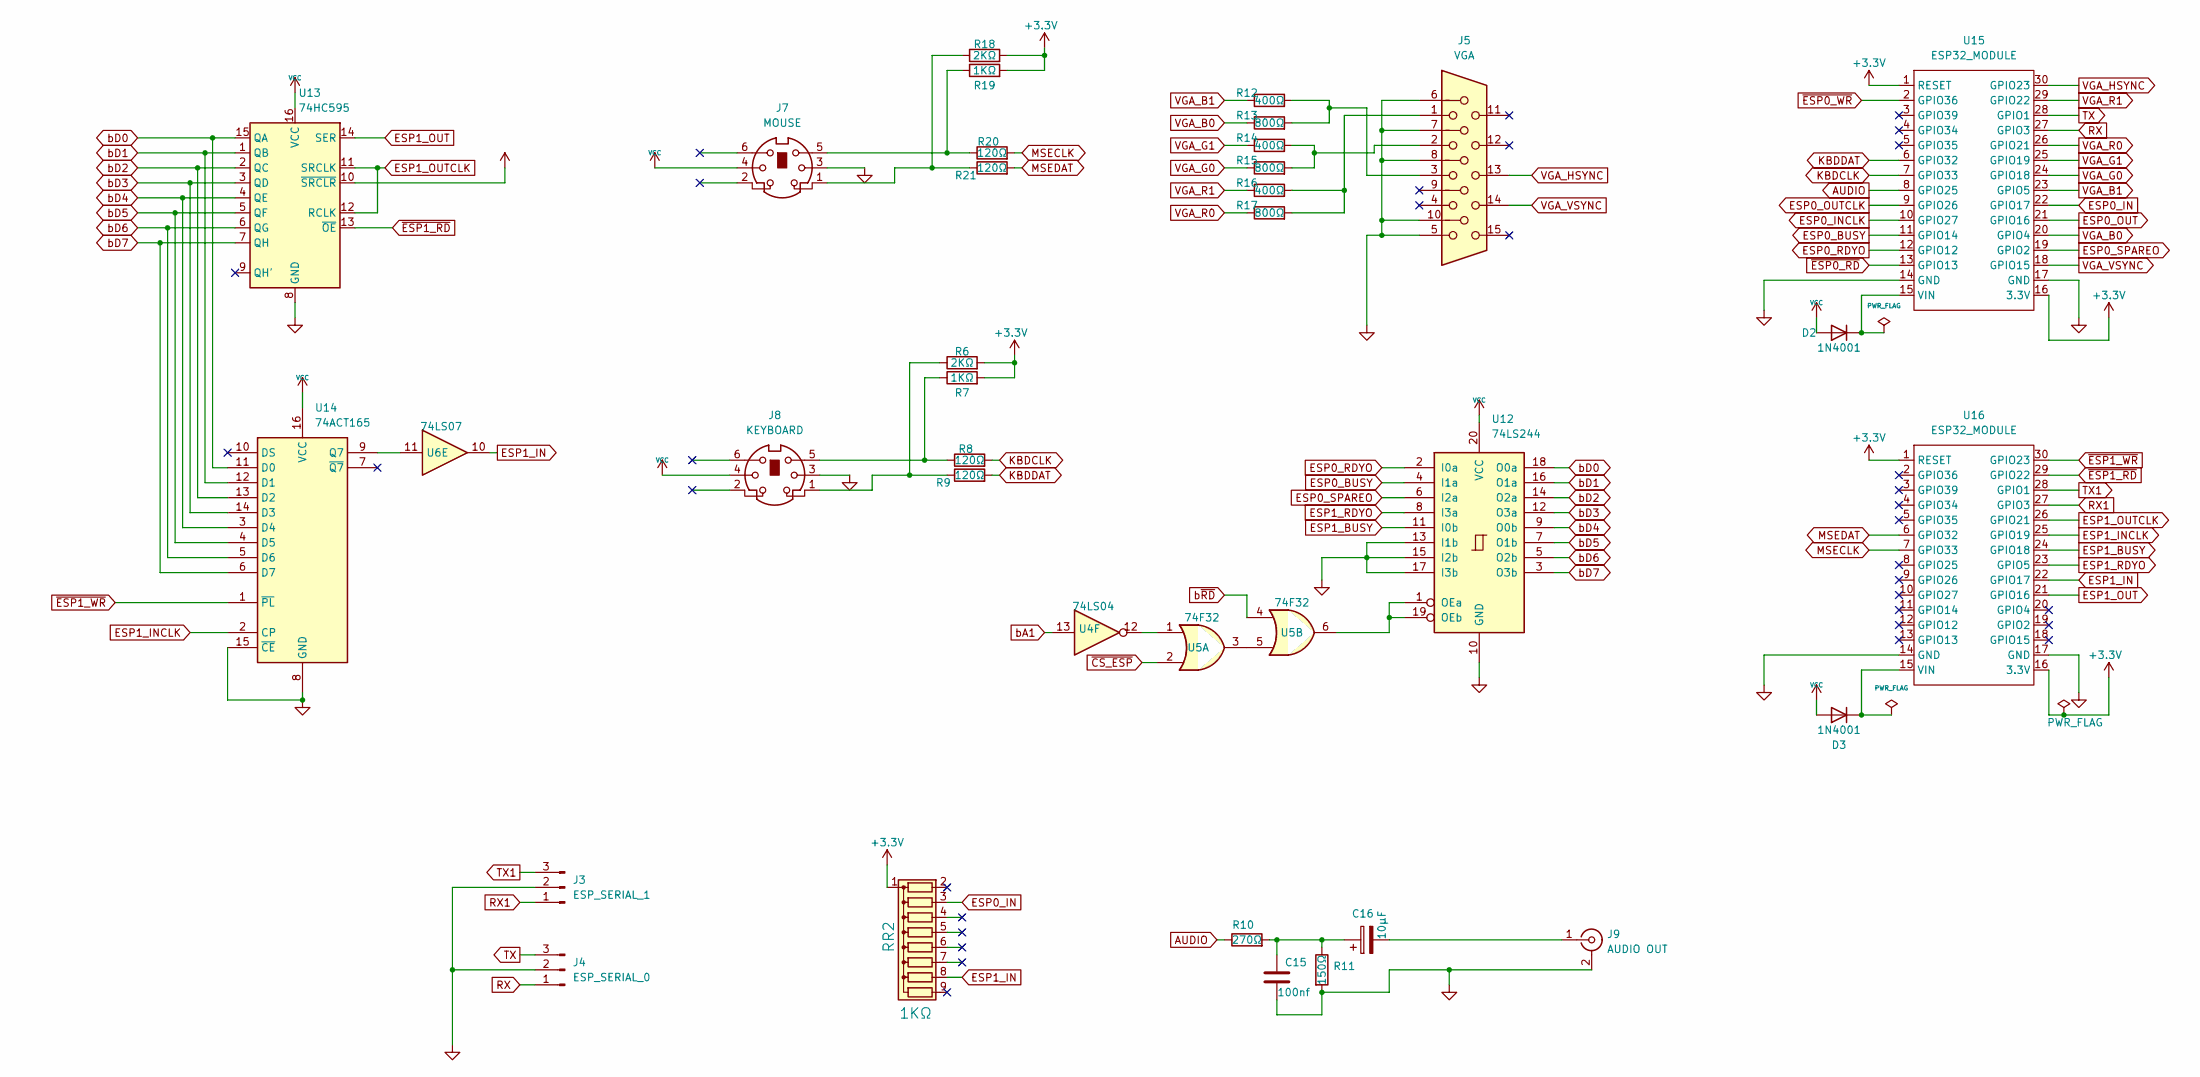
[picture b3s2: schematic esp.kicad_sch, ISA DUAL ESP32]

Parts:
C15: 100nf; STD_DDW_CAP
C16: 10µF; STD_DDW_PCAP
D2, D3: 1N4001; D_DO-41_SOD81_P10.16mm_Horizontal
J3: ESP_SERIAL_1; STD_DDW_PINHEAD_V_1x03
J4: ESP_SERIAL_0; STD_DDW_PINHEAD_V_1x03
J5: VGA; STD_DDW_VGA
J7: MOUSE; PS2_DIN
J8: KEYBOARD; PS2_DIN
J9: AUDIO OUT; STD_DDW_RCA
R6, R18: 2KΩ; STD_DDW_RESISTOR
R7, R19: 1KΩ; STD_DDW_RESISTOR
R8, R9, R20, R21: 120Ω; STD_DDW_RESISTOR
R10: 270Ω; STD_DDW_RESISTOR
R11: 150Ω; STD_DDW_RESISTOR
R12, R14, R16: 400Ω; STD_DDW_RESISTOR
R13, R15, R17: 800Ω; STD_DDW_RESISTOR
RR2: 1KΩ; R_Array_SIP9
U4: 74LS04; STD_DDW_DIP14
U5: 74F32; STD_DDW_DIP14
U6: 74LS07; STD_DDW_DIP14
U12: 74LS244; STD_DDW_DIP20
U13: 74HC595; STD_DDW_DIP16
U14: 74ACT165; STD_DDW_DIP16
U15, U16: ESP32_MODULE; ESP32_Module

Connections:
+3.3V: R6.2, R7.2, R18.2, R19.2, RR2.1 (common), U15.1 (RESET), U15.16 (3.3V), U16.1 (RESET), U16.16 (3.3V)
AUDIO: R10.1, U15.8 (GPIO25)
ESP0_BUSY: U12.4 (I1a), U15.11 (GPIO14)
ESP0_IN: RR2.3 (R2), U15.22 (GPIO17); also elsewhere on the board
ESP0_INCLK: U15.10 (GPIO27); also elsewhere on the board
ESP0_OUT: U15.21 (GPIO16); also elsewhere on the board
ESP0_OUTCLK: U15.9 (GPIO26); also elsewhere on the board
ESP0_RDYO: U12.2 (I0a), U15.12 (GPIO12)
ESP0_SPAREO: U12.6 (I2a), U15.19 (GPIO2)
ESP1_BUSY: U12.11 (I0b), U16.24 (GPIO18)
ESP1_IN: RR2.8 (R7), U6.10, U16.22 (GPIO17)
ESP1_INCLK: U14.2 (CP), U16.25 (GPIO19)
ESP1_OUT: U13.14 (SER), U16.21 (GPIO16)
ESP1_OUTCLK: U13.11 (SRCLK), U13.12 (RCLK), U16.26 (GPIO21)
ESP1_RDYO: U12.8 (I3a), U16.23 (GPIO5)
GND: C15.2, J3.2, J4.2, J5.5, J5.6, J5.7, J5.8, J5.10, J7.3, J8.3, J9.2 (Ext), R11.2, U12.10 (GND), U12.13 (I1b), U12.15 (I2b), U12.17 (I3b), U13.8 (GND), U14.8 (GND), U14.15 (~CE), U15.14 (GND), U15.17 (GND), U16.14 (GND), U16.17 (GND); also elsewhere on the board
KBDCLK: R8.2, U15.7 (GPIO33)
KBDDAT: R9.2, U15.6 (GPIO32)
MSECLK: R20.2, U16.7 (GPIO33)
MSEDAT: R21.2, U16.6 (GPIO32)
unnamed: C15.1, C16.1, R10.2, R11.1
unnamed: D2.1 (K), U15.15 (VIN)
unnamed: D3.1 (K), U16.15 (VIN)
unnamed: J5.1, R16.2, R17.2
unnamed: J5.2, R14.2, R15.2
unnamed: J5.3, R12.2, R13.2
unnamed: J7.1, R18.1, R21.1
unnamed: J7.5, R19.1, R20.1
unnamed: J8.1, R6.1, R9.1
unnamed: J8.5, R7.1, R8.1
unnamed: C16.2, J9.1 (In)
unnamed: U4.12, U5.1
unnamed: U5.3, U5.5
unnamed: U5.6, U12.1 (OEa), U12.19 (OEb)
unnamed: U6.11, U14.9 (Q7)
RX: J4.1, U15.27 (GPIO3)
RX1: J3.1, U16.27 (GPIO3)
TX: J4.3, U15.28 (GPIO1)
TX1: J3.3, U16.28 (GPIO1)
VCC: D2.2 (A), D3.2 (A), J7.4, J8.4, U12.20 (VCC), U13.10 (~SRCLR), U13.16 (VCC), U14.16 (VCC); also elsewhere on the board
VGA_B0: R13.1, U15.20 (GPIO4)
VGA_B1: R12.1, U15.23 (GPIO5)
VGA_G0: R15.1, U15.24 (GPIO18)
VGA_G1: R14.1, U15.25 (GPIO19)
VGA_HSYNC: J5.13, U15.30 (GPIO23)
VGA_R0: R17.1, U15.26 (GPIO21)
VGA_R1: R16.1, U15.29 (GPIO22)
VGA_VSYNC: J5.14, U15.18 (GPIO15)
bA1: U4.13; also elsewhere on the board
bD0: U12.18 (O0a), U13.15 (QA), U14.11 (D0); also elsewhere on the board
bD1: U12.16 (O1a), U13.1 (QB), U14.12 (D1); also elsewhere on the board
bD2: U12.14 (O2a), U13.2 (QC), U14.13 (D2); also elsewhere on the board
bD3: U12.12 (O3a), U13.3 (QD), U14.14 (D3); also elsewhere on the board
bD4: U12.9 (O0b), U13.4 (QE), U14.3 (D4); also elsewhere on the board
bD5: U12.7 (O1b), U13.5 (QF), U14.4 (D5); also elsewhere on the board
bD6: U12.5 (O2b), U13.6 (QG), U14.5 (D6); also elsewhere on the board
bD7: U12.3 (O3b), U13.7 (QH), U14.6 (D7); also elsewhere on the board
b~RD: U5.4; also elsewhere on the board
~CS_ESP: U5.2; also elsewhere on the board
~ESP0_RD: U15.13 (GPIO13); also elsewhere on the board
~ESP0_WR: U15.2 (GPIO36); also elsewhere on the board
~ESP1_RD: U13.13 (~OE), U16.29 (GPIO22); also elsewhere on the board
~ESP1_WR: U14.1 (~PL), U16.30 (GPIO23); also elsewhere on the board
